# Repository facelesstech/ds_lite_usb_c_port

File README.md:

# DS lite USB C port

Items you will need.
  * [6 pin USB C Port](https://www.aliexpress.com/item/32966491026.html?spm=a2g0o.productlist.0.0.40682b02dGnW8h&algo_pvid=d52f6c09-77d8-4ea5-9f91-3c1a38f8a389&algo_exp_id=d52f6c09-77d8-4ea5-9f91-3c1a38f8a389-0&pdp_ext_f=%7B%22sku_id%22%3A%2266546029161%22%7D&pdp_npi=2%40dis%21GBP%21%210.47%210.47%21%211.97%21%21%402100bdd716543375023874249e4539%2166546029161%21sea)
  * [5.1k 0603 SMD resistors x2](https://www.aliexpress.com/item/1005001436923851.html?spm=a2g0o.productlist.0.0.1dab6ecdFCRr6p&algo_pvid=8ccb23e2-83dc-4ed7-917b-6b67ea6ceffa&algo_exp_id=8ccb23e2-83dc-4ed7-917b-6b67ea6ceffa-0&pdp_ext_f=%7B%22sku_id%22%3A%2212000016109475033%22%7D&pdp_npi=2%40dis%21GBP%21%210.09%210.09%21%21%21%21%402100bde316543376141027916e302a%2112000016109475033%21sea)

# Assembly of the USB C charge port PCB

Remove the mouse bits from the PCB with a file. Place the USB C port into place and secure the anchor legs with some solder. Flip the PCB over and solder all 6 of the USB C port pins. Flux and a fine soldering iron tip is advised. Next solder in place the 5.1k 0603 smd resistors, Add solder to one side of the pads and with tweezers place the resistor and heat the solder to secure, If you are happy with the placement add solder to the other pad.

# Installing USB C charge port

Remove your old charge port, This can be done with a hot air work station.

Line the two bottom holes in the PCB up with the two holes in the ds lites charge port, Making sure that the USB C PCB doesn't stick out over the edge of the DS Lite PCB. Solder then into place. Test to see if your DS Lite charges with the new port, If so then solder the other 4 anchor points from the old charge port to secure the new PCB.

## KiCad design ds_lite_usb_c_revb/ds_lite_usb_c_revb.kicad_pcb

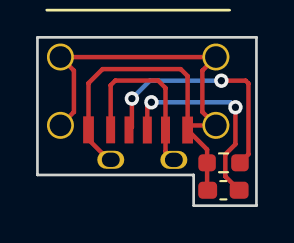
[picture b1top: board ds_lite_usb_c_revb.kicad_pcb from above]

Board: 2 copper layers, 12.2 x 9.4 mm, 4 parts (0 on the bottom side), 4 nets.

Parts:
R1: R; R_0603_1608Metric_Pad1.05x0.95mm_HandSolder
R2: R; R_0603_1608Metric_Pad0.98x0.95mm_HandSolder
U1: usb_c_6pin; USB_C_6PIN_custom
U2: battery_custom; ds_lite_charger_pins

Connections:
unnamed: R1.1, U1.4
unnamed: R1.2, R2.2, U1.1, U2.1
unnamed: R2.1, U1.3
unnamed: U1.2, U2.2

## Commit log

2022-05-29 setting the license
2022-05-29 kicad files
2022-06-02 added photos
2022-06-02 added photos to readme
2022-06-02 added photos to readme1
2022-06-02 added photos to readme2
2022-06-02 added photos to readme3
2022-06-02 added photos to readme4
2022-06-02 added photos to readme5
2022-06-04 added photos to readme6
2022-06-04 added a list
2022-06-04 added link to list
2022-06-04 added another link to list
2022-06-04 added more instructions
2022-06-04 formatting
2022-06-04 formatting1
2022-06-04 spelling
